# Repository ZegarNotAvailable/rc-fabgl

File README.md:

# rc-fabgl
 FabGL terminal board for RC2014

[SMD version](https://github.com/ZegarNotAvailable/rc-fabgl/tree/main/SMD-version/rc-fabgl-SMD)

## Overview
This is my take on the FabGL dev kit, designed into the form factor of a RC2014 card with the intention of implementing a serial terminal.

## FabGL
[FabGL](http://www.fabglib.org/) is an excellent graphics/UI/Human Interface library for the Espressif ESP32. It provides VGA display generation, PS2 keyboard/mouse support, audio, and terminal emulation abilities. This gives us everything we need to build a serial terminal (and even provides examples to do just this). In addition, the ESP32 is first and foremost a WiFi module, opening up the possibility of "dial" in/out cabibilities.

## The ESP32
The common ESP32-WROOM module starts to run a bit short on memory when implementing a terminal, so the ESP32-WROVER is used instead - this adds an extra 8MB of RAM for us to use. The module is hooked up as described in Espressif's datasheet, with RC reset circuit and appropriate bypass caps.

## Functions provided
The standard dev kit schematic provides VGA, PS/2 keyboard, PS/2 mouse and line-level audio. The mouse port is removed, audio is sent directly into a piezo buzzer, and level-shifted serial ports are added to connect to the 5V serial ports of RC2014 systems. In addition, improvements have been made to the other peripheral connections.

### VGA
120Ω resistors are added to terminate the VGA connection (and limit the HSync and VSync pins). The design is similar to the Parallax Propeller VGA breakout. The resistor values were picked to stay within the drive capabilities of the ESP32 (which is why the correct 75Ω resistors weren't an option).

### PS/2 keyboard
The resistor PS/2 level-shifters are replaced with MOSFET shifters.

### Audio
Audio won't be used for much more than a terminal bell - as such, it's just connected to a buzzer. Make sure a piezo buzzer is used - the ESP32 can't drive a dynamic one without help.

### Serial ports
Serial ports are connected to the remaining pins on the ESP32. There are enough pins to implement two serial ports, with RTS/CTS flow control on the second port. Incoming 5V signals are shifted down to 3.3V with a 74LV125.

## Programming port
The standard RX/TX pins of the ESP32 are broken out to a standard "FTDI-style" header for programming. RESET and BOOT are connected to buttons on the top of the card.

## Bus connection
The terminal board uses the RC2014 bus for little more than power and to connect to the bus serial ports. Jumpers are provided to disconnect the ports from the bus as needed. The Ser1 interface is provided to the bus only, while Ser2 is available on both the (Enhanced) bus and an FTDI-style header. Only the header provides the RTS & CTS pins. Since Ser2 is the *only* thing on the Enhanced bus, consider the wider connector optional - a cheaper 1x40 header can be used in place of the 2x40 one (you'll need a [6-pin Dupont cable](https://www.ebay.com/sch/i.html?_nkw=6+pin+dupont+cable) to hook up Ser2).

### Initial setup
The ESP32 module will need to be programmed before use - this is done using an FTDI adapter on the assembled board, via the *Prog* port. If you don't have an FTDI adapter, they can be [found on eBay](https://www.ebay.com/sch/i.html?_nkw=ftdi+adapter). I don't have a firmware bundle made up for this yet, so for now consider this a dev kit for hacking (as opposed to a plug-and-play terminal board). To get started with FabGL, check out Fabrizio Di Vittorio's [YouTube channel](https://www.youtube.com/user/fdivitto/videos) and the [FabGL reference](http://www.fabglib.org/). Compiling FabGL and its examples requires the [Arduino IDE](https://www.arduino.cc/en/software). Once Arduino is up and running, follow the instructions in [Fabrizio's video](https://www.youtube.com/watch?v=8OTaPQlSTas) to add the ESP32 board package and FabGL library. Be sure to select *ESP32 Wrover Module* from *Tools* → *Board* → *ESP32 Arduino*. Examples are found in *File* → *Examples* → *FabGL* → *VGA*. 

## Part selection
Bill Of Materials and part references are below. If you want the 60-pin RC2014 Enhanced bus connector, you'll need to make it from a 2x40-pin right-angle header and pull out half of the pins from the top row (needle-nose pliers work well). I recommend using gold-plated header for this - I use these ones from [Pololu](https://www.pololu.com/product/2668) or [Sparkfun](https://www.sparkfun.com/products/12792). The jumper headers can be snapped from regular (or double-row) breakaway header, for which eBay is substantially cheaper; the Mouser listings are provided for convenience.

The specified parts are just the ones I used, and can be substituted as needed - Mouser links provided for convenience and reference.

| Reference | Value | Qty | Mouser link |
| --------- | ----- | --- | ----------- |
| BZ1 | Piezo buzzer | 1 | [TDK PS1240P02BT](https://www.mouser.com/ProductDetail/810-PS1240P02BT) |
| C1 | 4.7μF ceramic | 1 | [TDK FG18X5R1E475KRT06](https://www.mouser.com/ProductDetail/FG18X5R1E475KRT06) |
| C2 | 1μF ceramic | 1 | [TDK FG18X5R1H105KRT06](https://www.mouser.com/ProductDetail/FG18X5R1H105KRT06) |
| C3 | 22μF electrolytic | 1 | [KEMET ESS226M016AC2AA](https://www.mouser.com/ProductDetail/ESS226M016AC2AA/) |
| C4 | 10μF ceramic | 1 | [TDK FG18X5R1E106MRT06](https://www.mouser.com/ProductDetail/FG18X5R1E106MRT06) |
| C5-C7 | 100nF ceramic | 3 | [KEMET C315C104M5U5TA](https://www.mouser.com/ProductDetail/C315C104M5U5TA7303) |
| J1/2 | 2x40 right-angle header | 1 | [3M 2380-5121TG](https://www.mouser.com/ProductDetail/2380-5121TG) |
| J3 | 2x6 right-angle header | 1 | [Amphenol 10129382-912002BLF](https://www.mouser.com/ProductDetail/10129382-912002BLF) |
| J4 | 6-pin Mini-DIN socket | 1 | [Kycon KMDGX-6S-BS](https://www.mouser.com/ProductDetail/806-KMDGX-6S-BS) |
| J5 | D-Sub HD-15 Female | 1 | [TE 2311763-1](https://www.mouser.com/ProductDetail/571-2311763-1) |
| JP1/2 | 2x2 header | 1 | [Amphenol 10129381-904002BLF](https://www.mouser.com/ProductDetail/10129381-904002BLF) |
| JP3/4/5/6 | 2x4 header | 1 | [Amphenol 10129381-908002BLF](https://www.mouser.com/ProductDetail/10129381-908002BLF) |
| Q1, Q2 | 2N7000 enh N-MOSFET | 2 | [ON Semi 2N7000](https://www.mouser.com/ProductDetail/2N7000) |
| R1 | 10kΩ resistor | 1 | [Yageo CFR-25JT-52-10K](https://www.mouser.com/ProductDetail/CFR-25JT-52-10K) |
| R2-R5 | 100kΩ resistor | 4 | [Yageo CFR-25JT-52-100K](https://www.mouser.com/ProductDetail/CFR-25JT-52-100K) |
| R6-R9 | 4k7Ω resistor | 4 | [Yageo CFR-25JT-52-4K7](https://www.mouser.com/ProductDetail/CFR-25JT-52-4K7) |
| R10-R14 | 120Ω resistor | 5 | [Yageo MFR-25FTF52-120R](https://www.mouser.com/ProductDetail/603-MFR-25FTF52-120R) |
| R15-R17 | 261Ω resistor | 3 | [Yageo MFR-25FRF52-261R](https://www.mouser.com/ProductDetail/603-MFR-25FRF52-261R) |
| R18-R20 | 510Ω resistor | 3 | [Yageo MFR-25FTE52-510R](https://www.mouser.com/ProductDetail/603-MFR-25FTE52-510R) |
| SW1, SW2 | Right-angle tact sw 3.9mm | 2 | [C&K PTS645VL392LFS](https://www.mouser.com/ProductDetail/611-PTS645VL392) |
| U1 | MCP1825S-330 | 1 | [Microchip MCP1825ST-3302E/DB](https://www.mouser.com/ProductDetail/579-MCP1825ST3302EDB) |
| U2 | ESP32-WROVER-E | 1 | [Espressif ESP32-WROVER-E(M213EH3264PH3Q0)](https://www.mouser.com/ProductDetail/356-ESP32WRVE23264PC) |
| U3 | 74LV125 | 1 | [TI SN74LV125AN](https://www.mouser.com/ProductDetail/595-SN74LV125AN) |

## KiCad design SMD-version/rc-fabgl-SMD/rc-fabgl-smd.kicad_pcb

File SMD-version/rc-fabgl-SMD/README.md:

# rc-fabgl

## SMD version.

## Overview
This is my take on the FabGL dev kit, designed into the form factor of a RC2014 card with the intention of implementing a serial terminal.

## FabGL
[FabGL](http://www.fabglib.org/) is an excellent graphics/UI/Human Interface library for the Espressif ESP32. It provides VGA display generation, PS2 keyboard/mouse support, audio, and terminal emulation abilities. This gives us everything we need to build a serial terminal (and even provides examples to do just this). In addition, the ESP32 is first and foremost a WiFi module, opening up the possibility of "dial" in/out cabibilities.

## The ESP32
The common ESP32-WROOM module starts to run a bit short on memory when implementing a terminal, so the ESP32-WROVER is used instead - this adds an extra 8MB of RAM for us to use. The module is hooked up as described in Espressif's datasheet, with RC reset circuit and appropriate bypass caps.

## Functions provided
The standard dev kit schematic provides VGA, PS/2 keyboard, PS/2 mouse and line-level audio. The mouse port is removed, audio is sent directly into a piezo buzzer, and level-shifted serial ports are added to connect to the 5V serial ports of RC2014 systems. In addition, improvements have been made to the other peripheral connections.

### VGA
120Ω resistors are added to terminate the VGA connection (and limit the HSync and VSync pins). The design is similar to the Parallax Propeller VGA breakout. The resistor values were picked to stay within the drive capabilities of the ESP32 (which is why the correct 75Ω resistors weren't an option).

### PS/2 keyboard
The resistor PS/2 level-shifters are replaced with MOSFET shifters.

### Audio
Audio won't be used for much more than a terminal bell - as such, it's just connected to a buzzer. Make sure a piezo buzzer is used - the ESP32 can't drive a dynamic one without help.

### Serial ports
Serial ports are connected to the remaining pins on the ESP32. There are enough pins to implement two serial ports, with RTS/CTS flow control on the second port. Incoming 5V signals are shifted down to 3.3V with a 74LV125.

## Programming port
The standard RX/TX pins of the ESP32 are broken out to a standard "FTDI-style" header for programming. RESET and BOOT are connected to buttons on the top of the card.

## Bus connection
The terminal board uses the RC2014 bus for little more than power and to connect to the bus serial ports. Jumpers are provided to disconnect the ports from the bus as needed. The Ser1 interface is provided to the bus only, while Ser2 is available on both the (Enhanced) bus and an FTDI-style header. Only the header provides the RTS & CTS pins. Since Ser2 is the *only* thing on the Enhanced bus, consider the wider connector optional - a cheaper 1x40 header can be used in place of the 2x40 one (you'll need a [6-pin Dupont cable](https://www.ebay.com/sch/i.html?_nkw=6+pin+dupont+cable) to hook up Ser2).

### Initial setup
The ESP32 module will need to be programmed before use - this is done using an FTDI adapter on the assembled board, via the *Prog* port. If you don't have an FTDI adapter, they can be [found on eBay](https://www.ebay.com/sch/i.html?_nkw=ftdi+adapter). I don't have a firmware bundle made up for this yet, so for now consider this a dev kit for hacking (as opposed to a plug-and-play terminal board). To get started with FabGL, check out Fabrizio Di Vittorio's [YouTube channel](https://www.youtube.com/user/fdivitto/videos) and the [FabGL reference](http://www.fabglib.org/). Compiling FabGL and its examples requires the [Arduino IDE](https://www.arduino.cc/en/software). Once Arduino is up and running, follow the instructions in [Fabrizio's video](https://www.youtube.com/watch?v=8OTaPQlSTas) to add the ESP32 board package and FabGL library. Be sure to select *ESP32 Wrover Module* from *Tools* → *Board* → *ESP32 Arduino*. Examples are found in *File* → *Examples* → *FabGL* → *VGA*. 

## Part selection
Bill Of Materials and part references are below. If you want the 60-pin RC2014 Enhanced bus connector, you'll need to make it from a 2x40-pin right-angle header and pull out half of the pins from the top row (needle-nose pliers work well). I recommend using gold-plated header for this - I use these ones from [Pololu](https://www.pololu.com/product/2668) or [Sparkfun](https://www.sparkfun.com/products/12792). The jumper headers can be snapped from regular (or double-row) breakaway header, for which eBay is substantially cheaper; the Mouser listings are provided for convenience.

The specified parts are just the ones I used, and can be substituted as needed - Mouser links provided for convenience and reference.

| Reference | Value | Qty | Mouser link |
| --------- | ----- | --- | ----------- |
| BZ1 | Piezo buzzer | 1 | [TDK PS1240P02BT](https://www.mouser.com/ProductDetail/810-PS1240P02BT) |
| C1 | 4.7μF ceramic | 1 | [TDK FG18X5R1E475KRT06](https://www.mouser.com/ProductDetail/FG18X5R1E475KRT06) |
| C2 | 1μF ceramic | 1 | [TDK FG18X5R1H105KRT06](https://www.mouser.com/ProductDetail/FG18X5R1H105KRT06) |
| C3 | 22μF electrolytic | 1 | [KEMET ESS226M016AC2AA](https://www.mouser.com/ProductDetail/ESS226M016AC2AA/) |
| C4 | 10μF ceramic | 1 | [TDK FG18X5R1E106MRT06](https://www.mouser.com/ProductDetail/FG18X5R1E106MRT06) |
| C5-C7 | 100nF ceramic | 3 | [KEMET C315C104M5U5TA](https://www.mouser.com/ProductDetail/C315C104M5U5TA7303) |
| J1/2 | 2x40 right-angle header | 1 | [3M 2380-5121TG](https://www.mouser.com/ProductDetail/2380-5121TG) |
| J3 | 2x6 right-angle header | 1 | [Amphenol 10129382-912002BLF](https://www.mouser.com/ProductDetail/10129382-912002BLF) |
| J4 | 6-pin Mini-DIN socket | 1 | [Kycon KMDGX-6S-BS](https://www.mouser.com/ProductDetail/806-KMDGX-6S-BS) |
| J5 | D-Sub HD-15 Female | 1 | [TE 2311763-1](https://www.mouser.com/ProductDetail/571-2311763-1) |
| JP1/2 | 2x2 header | 1 | [Amphenol 10129381-904002BLF](https://www.mouser.com/ProductDetail/10129381-904002BLF) |
| JP3/4/5/6 | 2x4 header | 1 | [Amphenol 10129381-908002BLF](https://www.mouser.com/ProductDetail/10129381-908002BLF) |
| Q1, Q2 | 2N7000 enh N-MOSFET | 2 | [ON Semi 2N7000](https://www.mouser.com/ProductDetail/2N7000) |
| R1 | 10kΩ resistor | 1 | [Yageo CFR-25JT-52-10K](https://www.mouser.com/ProductDetail/CFR-25JT-52-10K) |
| R2-R5 | 100kΩ resistor | 4 | [Yageo CFR-25JT-52-100K](https://www.mouser.com/ProductDetail/CFR-25JT-52-100K) |
| R6-R9 | 4k7Ω resistor | 4 | [Yageo CFR-25JT-52-4K7](https://www.mouser.com/ProductDetail/CFR-25JT-52-4K7) |
| R10-R14 | 120Ω resistor | 5 | [Yageo MFR-25FTF52-120R](https://www.mouser.com/ProductDetail/603-MFR-25FTF52-120R) |
| R15-R17 | 261Ω resistor | 3 | [Yageo MFR-25FRF52-261R](https://www.mouser.com/ProductDetail/603-MFR-25FRF52-261R) |
| R18-R20 | 510Ω resistor | 3 | [Yageo MFR-25FTE52-510R](https://www.mouser.com/ProductDetail/603-MFR-25FTE52-510R) |
| SW1, SW2 | Right-angle tact sw 3.9mm | 2 | [C&K PTS645VL392LFS](https://www.mouser.com/ProductDetail/611-PTS645VL392) |
| U1 | MCP1825S-330 | 1 | [Microchip MCP1825ST-3302E/DB](https://www.mouser.com/ProductDetail/579-MCP1825ST3302EDB) |
| U2 | ESP32-WROVER-E | 1 | [Espressif ESP32-WROVER-E(M213EH3264PH3Q0)](https://www.mouser.com/ProductDetail/356-ESP32WRVE23264PC) |
| U3 | 74LV125 | 1 | [TI SN74LV125AN](https://www.mouser.com/ProductDetail/595-SN74LV125AN) |

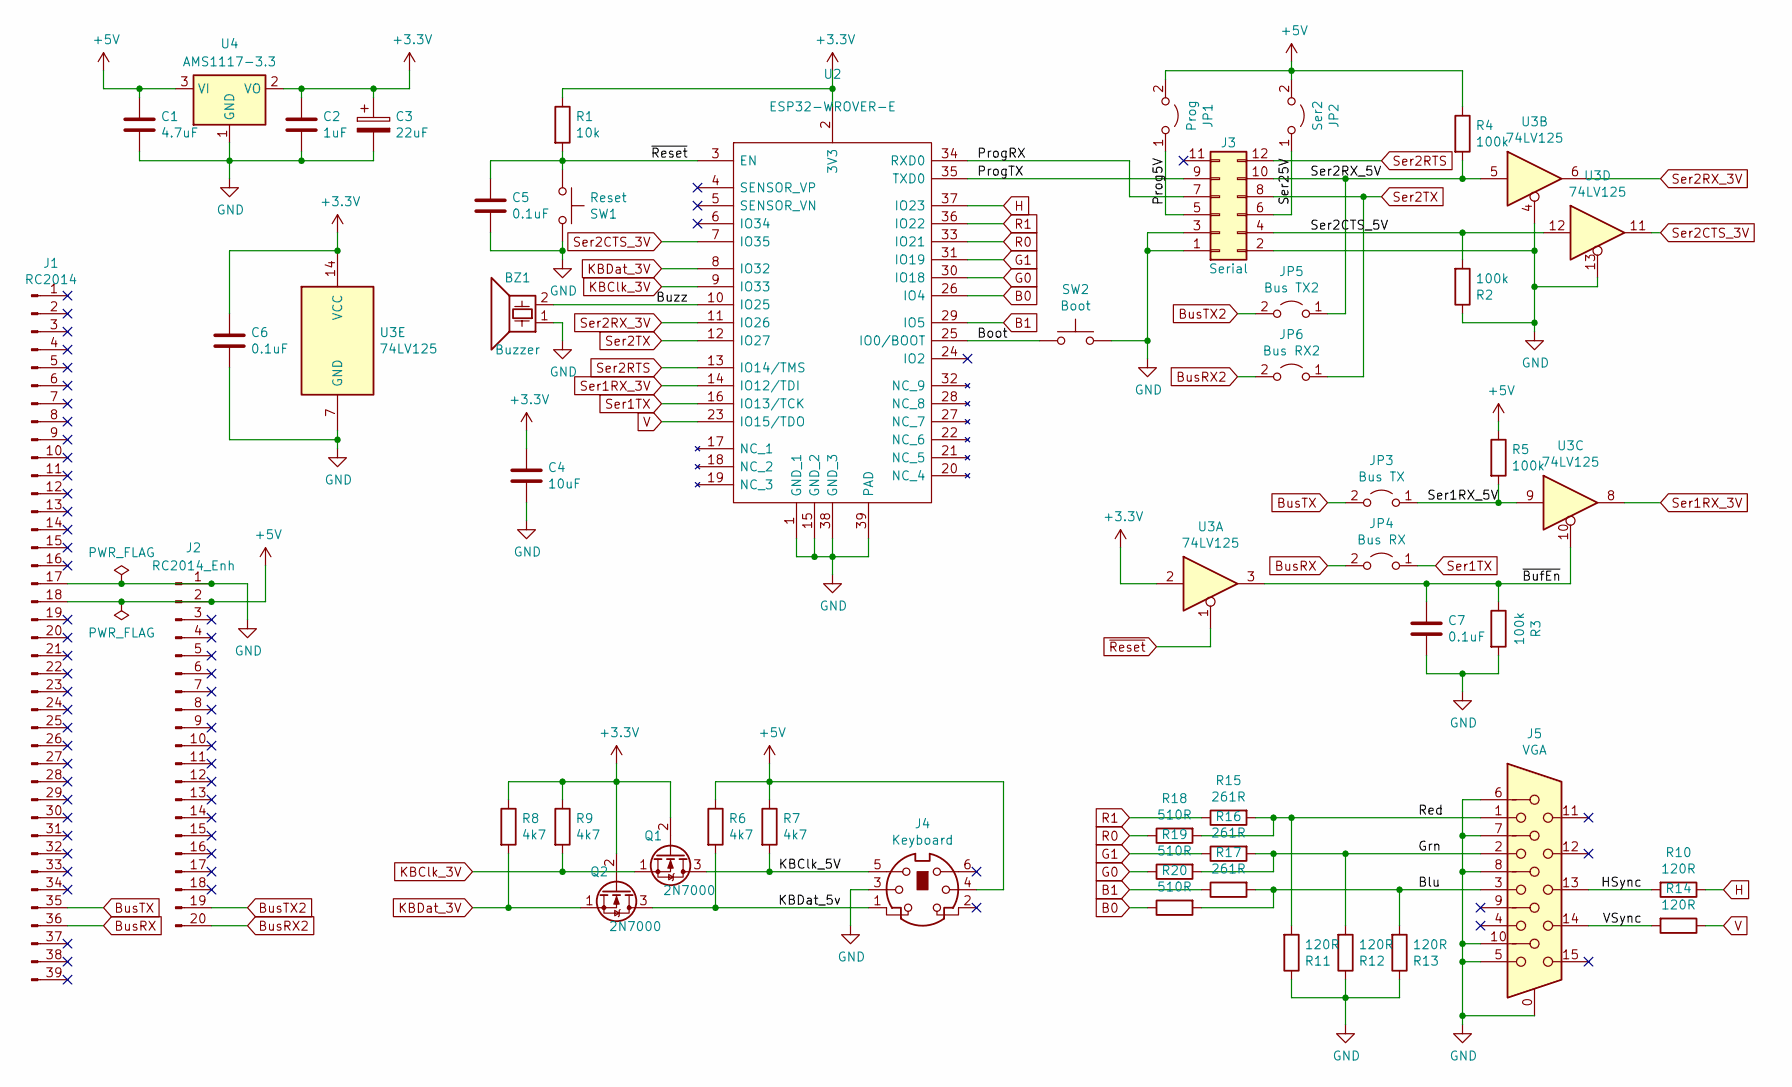
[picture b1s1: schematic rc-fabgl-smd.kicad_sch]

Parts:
BZ1: Buzzer; Buzzer_TDK_PS1240P02BT_D12.2mm_H6.5mm
C1: 4.7uF; C_Disc_D3.4mm_W2.1mm_P2.50mm
C2: 1uF; C_Disc_D3.0mm_W1.6mm_P2.50mm
C3: 22uF; CP_Radial_D5.0mm_P2.00mm
C4: 10uF; C_Disc_D3.4mm_W2.1mm_P2.50mm
C5, C6, C7: 0.1uF; C_Disc_D3.0mm_W1.6mm_P2.50mm
J1: RC2014; PinHeader_1x39_P2.54mm_Vertical
J2: RC2014_Enh; PinHeader_1x20_P2.54mm_Vertical
J3: Serial; PinHeader_2x06_P2.54mm_Horizontal
J4: Keyboard; Mini-DIN-6-Socket
J5: VGA; DSUB-15-HD_Female_Horizontal_P2.29x2.54mm_Housed
JP1: Prog; PinHeader_1x02_P2.54mm_Vertical
JP2: Ser2; PinHeader_1x02_P2.54mm_Vertical
JP3: Bus TX; PinHeader_1x02_P2.54mm_Vertical
JP4: Bus RX; PinHeader_1x02_P2.54mm_Vertical
JP5: Bus TX2; PinHeader_1x02_P2.54mm_Vertical
JP6: Bus RX2; PinHeader_1x02_P2.54mm_Vertical
Q1, Q2: 2N7000; TO-92
R1: 10k; R_Axial_DIN0207_L6.3mm_D2.5mm_P7.62mm_Horizontal
R2, R3, R4, R5: 100k; R_Axial_DIN0207_L6.3mm_D2.5mm_P7.62mm_Horizontal
R6, R7, R8, R9: 4k7; R_Axial_DIN0207_L6.3mm_D2.5mm_P7.62mm_Horizontal
R10, R11, R12, R13, R14: 120R; R_Axial_DIN0207_L6.3mm_D2.5mm_P7.62mm_Horizontal
R15, R16, R17: 261R; R_Axial_DIN0207_L6.3mm_D2.5mm_P7.62mm_Horizontal
R18, R19, R20: 510R; R_Axial_DIN0207_L6.3mm_D2.5mm_P7.62mm_Horizontal
SW1: Reset; SW_Tactile_SPST_Angled_PTS645Vx39-2LFS
SW2: Boot; SW_Tactile_SPST_Angled_PTS645Vx39-2LFS
U2: ESP32-WROVER-E; ESP32WROVERE
U3: 74LV125; SO-14_3.9x8.65mm_P1.27mm
U4: AMS1117-3.3; SOT-223-3_TabPin2

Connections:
+3V3: C2.1, C3.1, C4.1, C6.1, Q1.2 (G), Q2.2 (G), R1.1, R8.1, R9.1, U2.2 (3V3), U3.2, U3.14 (VCC), U4.2 (VO)
+5V: C1.1, J1.18, J2.2, J4.4, JP1.2 (B), JP2.2 (B), R4.1, R5.1, R6.1, R7.1, U4.3 (VI)
/Blu: J5.3, R13.2, R17.2, R20.2
/Boot: SW2.1, U2.25 (IO0/BOOT)
/Buzz: BZ1.2, U2.10 (IO25)
/Grn: J5.2, R12.2, R16.2, R19.2
/HSync: J5.13, R10.2
/KBClk_5V: J4.5, Q1.3 (D), R7.2
/KBDat_5v: J4.1, Q2.3 (D), R6.2
/Prog5V: J3.5, JP1.1 (A)
/ProgRX: J3.7, U2.34 (RXD0)
/ProgTX: J3.9, U2.35 (TXD0)
/Red: J5.1, R11.2, R15.2, R18.2
/Ser1RX_5V: JP3.1 (A), R5.2, U3.9
/Ser2CTS_5V: J3.4, R2.2, U3.12
/Ser2RX_5V: J3.10, JP5.1 (A), R4.2, U3.5
/Ser25V: J3.6, JP2.1 (A)
/VSync: J5.14, R14.2
/~BufEn: C7.2, R3.1, U3.3, U3.10
B0: R20.1, U2.26 (IO4)
B1: R17.1, U2.29 (IO5)
BusRX: J1.36, JP4.2 (B)
BusRX2: J2.20, JP6.2 (B)
BusTX: J1.35, JP3.2 (B)
BusTX2: J2.19, JP5.2 (B)
G0: R19.1, U2.30 (IO18)
G1: R16.1, U2.31 (IO19)
GND: BZ1.1, C1.2, C2.2, C3.2, C4.2, C5.2, C6.2, C7.1, J1.17, J2.1, J3.1, J3.2, J3.3, J4.3, J5.0, J5.5, J5.6, J5.7, J5.8, J5.10, R2.1, R3.2, R11.1, R12.1, R13.1, SW1.1, SW2.2, U2.1 (GND_1), U2.15 (GND_2), U2.38 (GND_3), U2.39 (PAD), U3.4, U3.7 (GND), U3.13, U4.1 (GND)
H: R10.1, U2.37 (IO23)
KBClk_3V: Q1.1 (S), R9.2, U2.9 (IO33)
KBDat_3V: Q2.1 (S), R8.2, U2.8 (IO32)
R0: R18.1, U2.33 (IO21)
R1: R15.1, U2.36 (IO22)
Ser1RX_3V: U2.14 (IO12/TDI), U3.8
Ser1TX: JP4.1 (A), U2.16 (IO13/TCK)
Ser2CTS_3V: U2.7 (IO35), U3.11
Ser2RTS: J3.12, U2.13 (IO14/TMS)
Ser2RX_3V: U2.11 (IO26), U3.6
Ser2TX: J3.8, JP6.1 (A), U2.12 (IO27)
V: R14.1, U2.23 (IO15/TDO)
~Reset: C5.1, R1.2, SW1.2, U2.3 (EN), U3.1

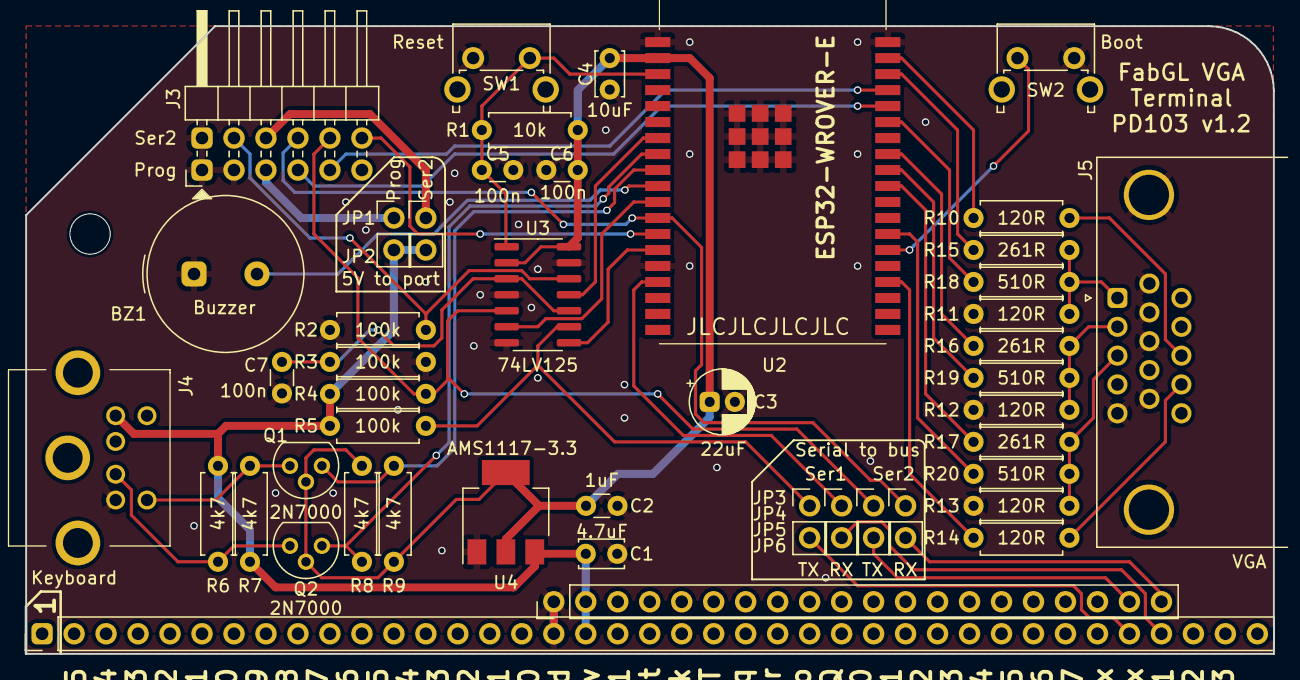
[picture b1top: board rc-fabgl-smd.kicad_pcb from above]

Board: 2 copper layers, 99.1 x 49.9 mm, 46 parts (0 on the bottom side), 41 nets.

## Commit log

2024-06-02 Initial commit.
2024-06-30 Add some pictures
2026-02-14 some adds
